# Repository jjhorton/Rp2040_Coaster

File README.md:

# Rp2040_Coaster

## Introduction
The idea was to build a light up drinks coaster, which would sit under a clear glass drinks bottle and light it up in a colorful display, only when the bottle is on top. 

## Building 

The main circuit is built around a [RP2040](https://www.raspberrypi.com/documentation/microcontrollers/rp2040.html), using the WS2812B "Neopixels" as the LEDs to create the colours, and a USB-C connector for power and programming. The PCB is designed using Kicad, and makes use of a simple 2 layer PCB, the examples here are made using JLCPCB, but any should work. 

The control software is written in C and is based of the PIO example from the Raspberry Pi example repo, the colours are generated based on the inputs of the 4 switches under the PCB. If two of the 4 switches are on, the light display begins, fading between pre-generated color pattern, which repeats. 

The PCB is placed under a 3d Printed case, this protects the PCB and electronics from any liquid or condensation on a cold bottle, the case is designed using openscad and the examples shown were printed on an Ender3 3D printed, and it should be possible to produce with most cheap 3D printers. 

## Testing

The software and PCB's fabrication files are built using Github actions, and the artifacts file contains a build of the latest software for uploading to the RP2040 and Gerbers that can be used to produced the PCB's using  

For the case, using the OpenSCAD files in the repo, they are automatically converted into a STL file using a seperate github workflow, with the files downloadable as an artifact from the last time they were run. 

## License 

Code: BSD-3-Clause

PCB/3D Model: CERN Open Hardware Licence Version 2 - Permissive

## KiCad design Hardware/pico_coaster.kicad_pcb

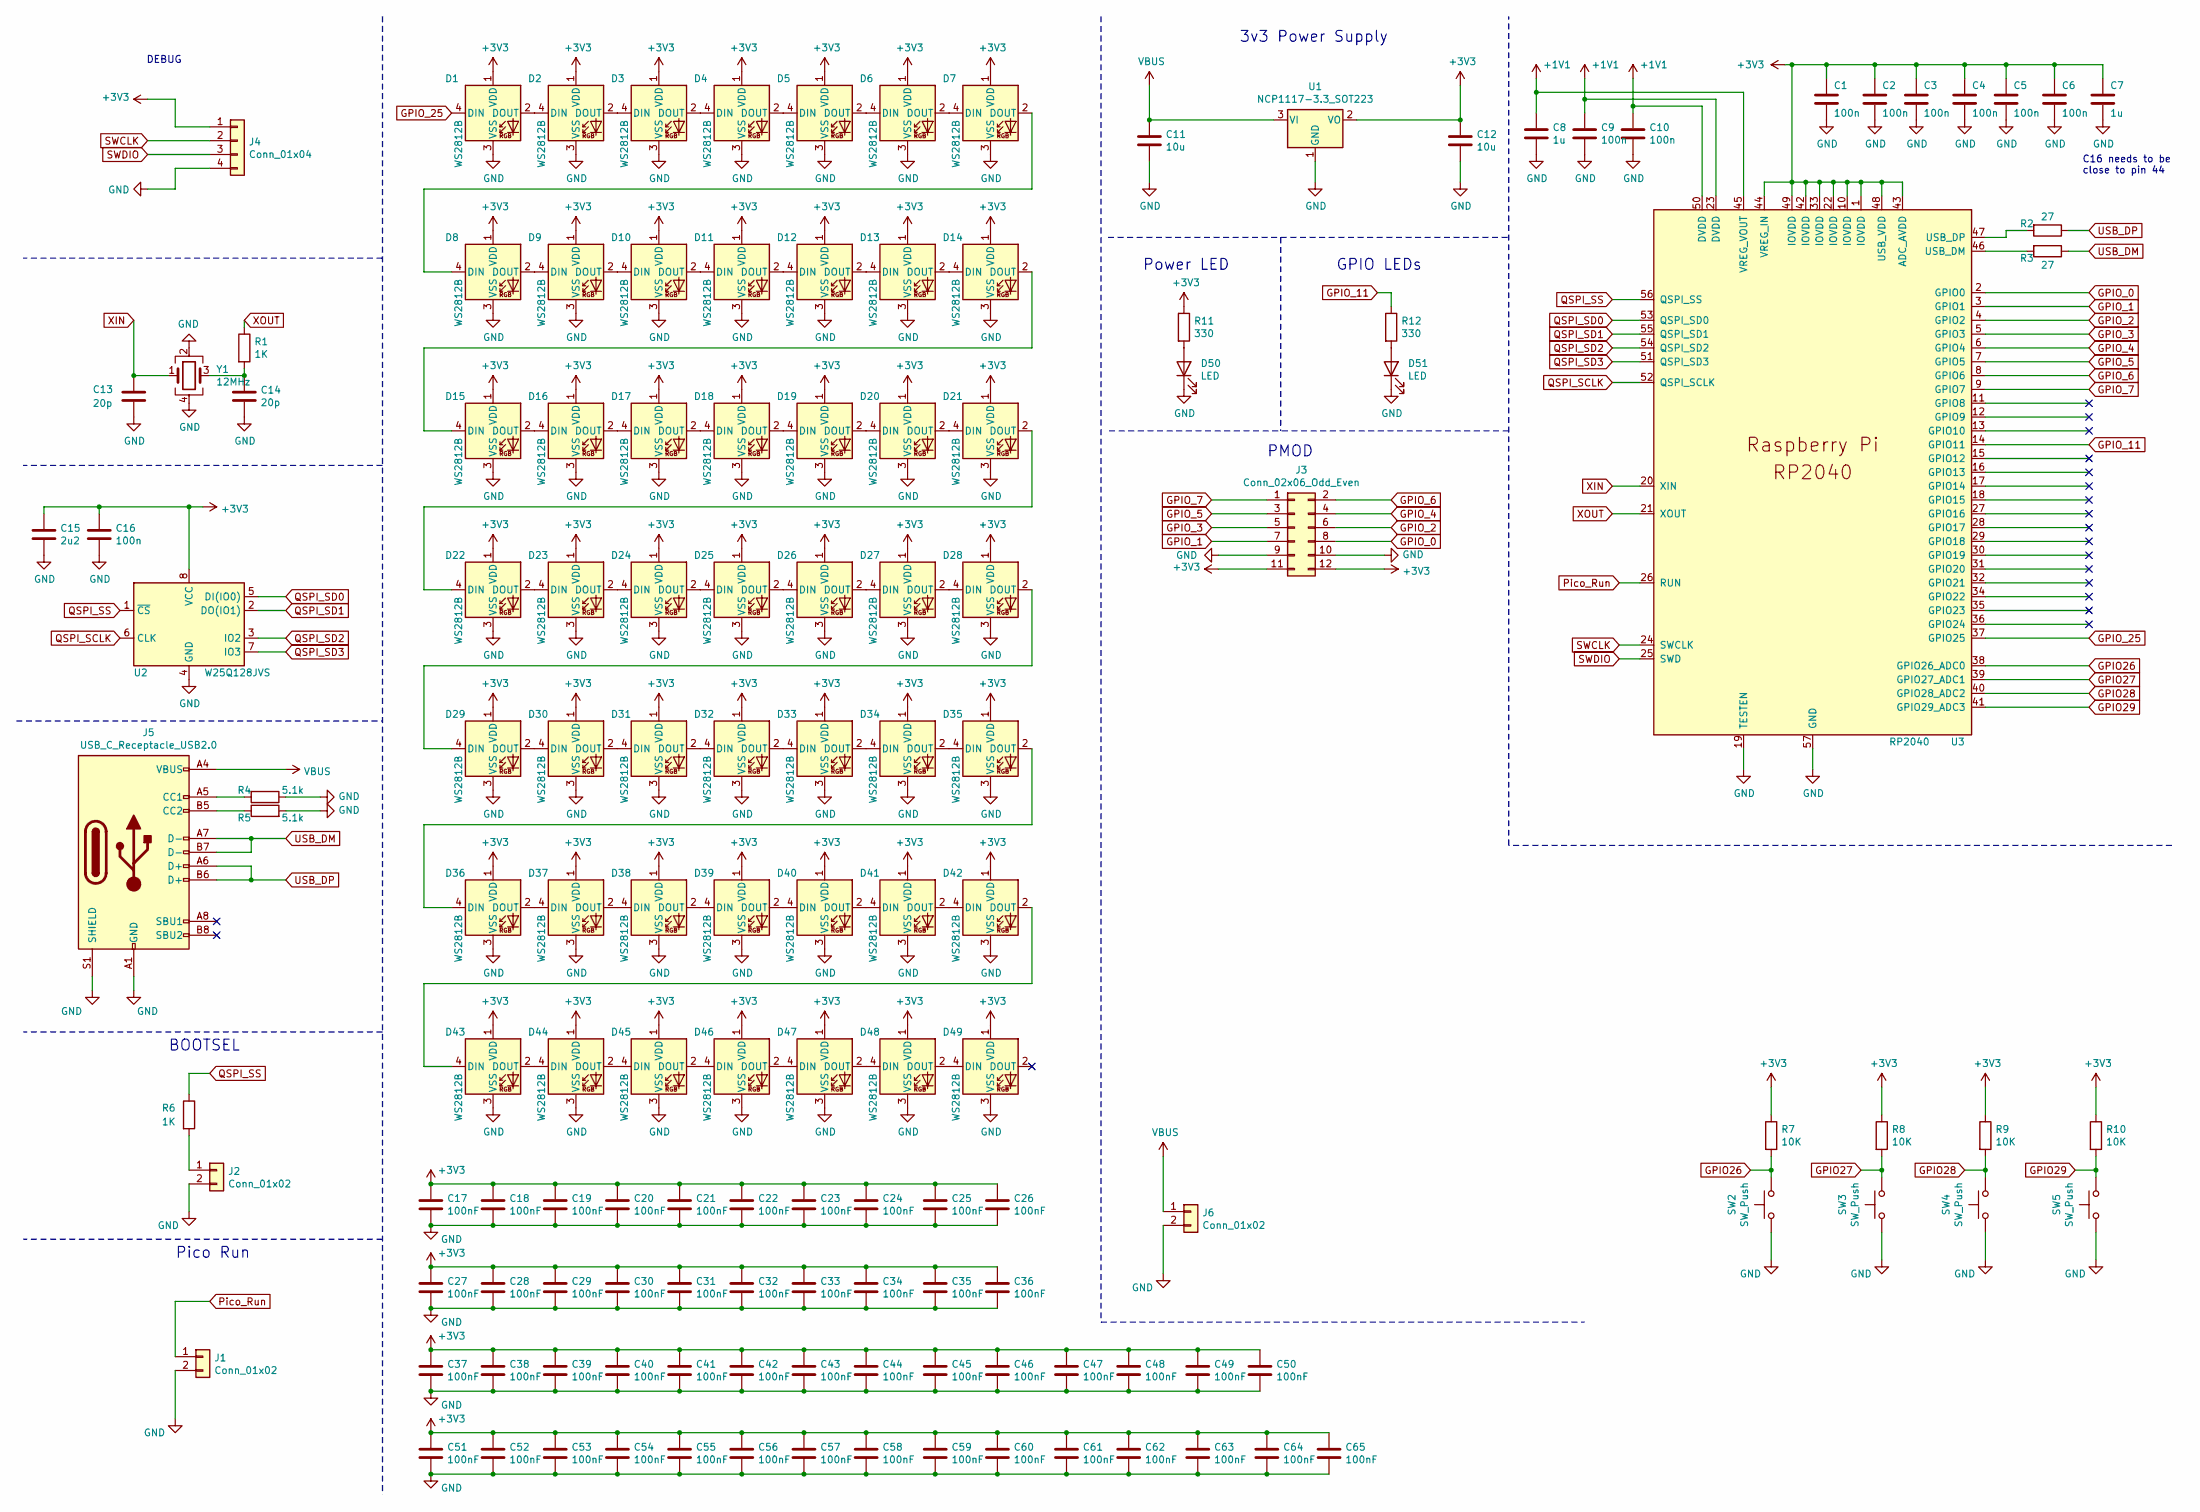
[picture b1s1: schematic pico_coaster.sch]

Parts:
C1, C2, C3, C4, C5, C6, C9, C10, C16: 100n; C_0603_1608Metric
C7, C8: 1u; C_0603_1608Metric
C11, C12: 10u; C_0603_1608Metric
C13, C14: 20p; C_0603_1608Metric
C15: 2u2; C_0603_1608Metric
C17, C18, C19, C20, C21, C22, C23, C24, C25, C26, C27, C28, C29, C30, C31, C32, C33, C34, C35, C36, C37, C38, C39, C40, C41, C42, C43, C44, C45, C46, C47, C48, C49, C50, C51, C52, C53, C54, C55, C56, C57, C58, C59, C60, C61, C62, C63, C64, C65: 100nF; C_0603_1608Metric
D1, D2, D3, D4, D5, D6, D7, D8, D9, D10, D11, D12, D13, D14, D15, D16, D17, D18, D19, D20, D21, D22, D23, D24, D25, D26, D27, D28, D29, D30, D31, D32, D33, D34, D35, D36, D37, D38, D39, D40, D41, D42, D43, D44, D45, D46, D47, D48, D49: WS2812B; LED_WS2812B_PLCC4_5.0x5.0mm_P3.2mm
D50, D51: LED; LED_0603_1608Metric
J1, J2, J6: Conn_01x02; PinHeader_1x02_P2.54mm_Horizontal
J3: Conn_02x06_Odd_Even; PinHeader_2x06_P2.54mm_Vertical
J4: Conn_01x04; PinHeader_1x04_P2.54mm_Vertical
J5: USB_C_Receptacle_USB2.0; USB_C_Receptacle_Amphenol_12401610E4-2A_CircularHoles
R1, R6: 1K; R_0603_1608Metric
R2, R3: 27; R_0603_1608Metric
R4, R5: 5.1k; R_0603_1608Metric
R7, R8, R9, R10: 10K; R_0603_1608Metric
R11, R12: 330; R_0603_1608Metric
SW2, SW3, SW4, SW5: SW_Push; SW_PUSH_6mm_H4.3mm
U1: NCP1117-3.3_SOT223; SOT-223-3_TabPin2
U2: W25Q128JVS; SOIC-8_5.23x5.23mm_P1.27mm
U3: RP2040; RP2040-QFN-56
Y1: 12MHz; Crystal_SMD_SeikoEpson_FA238-4Pin_3.2x2.5mm

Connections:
+1V1: C8.1, C9.1, C10.1, U3.23 (DVDD), U3.45 (VREG_VOUT), U3.50 (DVDD)
+3V3: C1.1, C2.1, C3.1, C4.1, C5.1, C6.1, C7.1, C12.1, C15.1, C16.1, C17.1, C18.1, C19.1, C20.1, C21.1, C22.1, C23.1, C24.1, C25.1, C26.1, C27.1, C28.1, C29.1, C30.1, C31.1, C32.1, C33.1, C34.1, C35.1, C36.1, C37.1, C38.1, C39.1, C40.1, C41.1, C42.1, C43.1, C44.1, C45.1, C46.1, C47.1, C48.1, C49.1, C50.1, C51.1, C52.1, C53.1, C54.1, C55.1, C56.1, C57.1, C58.1, C59.1, C60.1, C61.1, C62.1, C63.1, C64.1, C65.1, D1.1 (VDD), D2.1 (VDD), D3.1 (VDD), D4.1 (VDD), D5.1 (VDD), D6.1 (VDD), D7.1 (VDD), D8.1 (VDD), D9.1 (VDD), D10.1 (VDD), D11.1 (VDD), D12.1 (VDD), D13.1 (VDD), D14.1 (VDD), D15.1 (VDD), D16.1 (VDD), D17.1 (VDD), D18.1 (VDD), D19.1 (VDD), D20.1 (VDD), D21.1 (VDD), D22.1 (VDD), D23.1 (VDD), D24.1 (VDD), D25.1 (VDD), D26.1 (VDD), D27.1 (VDD), D28.1 (VDD), D29.1 (VDD), D30.1 (VDD), D31.1 (VDD), D32.1 (VDD), D33.1 (VDD), D34.1 (VDD), D35.1 (VDD), D36.1 (VDD), D37.1 (VDD), D38.1 (VDD), D39.1 (VDD), D40.1 (VDD), D41.1 (VDD), D42.1 (VDD), D43.1 (VDD), D44.1 (VDD), D45.1 (VDD), D46.1 (VDD), D47.1 (VDD), D48.1 (VDD), D49.1 (VDD), J3.11, J3.12, J4.1, R7.1, R8.1, R9.1, R10.1, R11.1, U1.2 (VO), U2.8 (VCC), U3.1 (IOVDD), U3.10 (IOVDD), U3.22 (IOVDD), U3.33 (IOVDD), U3.42 (IOVDD), U3.43 (ADC_AVDD), U3.44 (VREG_IN), U3.48 (USB_VDD), U3.49 (IOVDD)
GND: C1.2, C2.2, C3.2, C4.2, C5.2, C6.2, C7.2, C8.2, C9.2, C10.2, C11.2, C12.2, C13.2, C14.2, C15.2, C16.2, C17.2, C18.2, C19.2, C20.2, C21.2, C22.2, C23.2, C24.2, C25.2, C26.2, C27.2, C28.2, C29.2, C30.2, C31.2, C32.2, C33.2, C34.2, C35.2, C36.2, C37.2, C38.2, C39.2, C40.2, C41.2, C42.2, C43.2, C44.2, C45.2, C46.2, C47.2, C48.2, C49.2, C50.2, C51.2, C52.2, C53.2, C54.2, C55.2, C56.2, C57.2, C58.2, C59.2, C60.2, C61.2, C62.2, C63.2, C64.2, C65.2, D1.3 (VSS), D2.3 (VSS), D3.3 (VSS), D4.3 (VSS), D5.3 (VSS), D6.3 (VSS), D7.3 (VSS), D8.3 (VSS), D9.3 (VSS), D10.3 (VSS), D11.3 (VSS), D12.3 (VSS), D13.3 (VSS), D14.3 (VSS), D15.3 (VSS), D16.3 (VSS), D17.3 (VSS), D18.3 (VSS), D19.3 (VSS), D20.3 (VSS), D21.3 (VSS), D22.3 (VSS), D23.3 (VSS), D24.3 (VSS), D25.3 (VSS), D26.3 (VSS), D27.3 (VSS), D28.3 (VSS), D29.3 (VSS), D30.3 (VSS), D31.3 (VSS), D32.3 (VSS), D33.3 (VSS), D34.3 (VSS), D35.3 (VSS), D36.3 (VSS), D37.3 (VSS), D38.3 (VSS), D39.3 (VSS), D40.3 (VSS), D41.3 (VSS), D42.3 (VSS), D43.3 (VSS), D44.3 (VSS), D45.3 (VSS), D46.3 (VSS), D47.3 (VSS), D48.3 (VSS), D49.3 (VSS), D50.1 (K), D51.1 (K), J1.2, J2.2, J3.9, J3.10, J4.4, J5.A1 (GND), J5.A12 (GND), J5.B1 (GND), J5.B12 (GND), J5.S1 (SHIELD), J6.2, R4.1, R5.2, SW2.1, SW3.1, SW4.1, SW5.1, U1.1 (GND), U2.4 (GND), U3.19 (TESTEN), U3.57 (GND), Y1.2, Y1.4
GPIO26: R7.2, SW2.2, U3.38 (GPIO26_ADC0)
GPIO27: R8.2, SW3.2, U3.39 (GPIO27_ADC1)
GPIO28: R9.2, SW4.2, U3.40 (GPIO28_ADC2)
GPIO29: R10.2, SW5.2, U3.41 (GPIO29_ADC3)
GPIO_0: J3.8, U3.2 (GPIO0)
GPIO_1: J3.7, U3.3 (GPIO1)
GPIO_2: J3.6, U3.4 (GPIO2)
GPIO_3: J3.5, U3.5 (GPIO3)
GPIO_4: J3.4, U3.6 (GPIO4)
GPIO_5: J3.3, U3.7 (GPIO5)
GPIO_6: J3.2, U3.8 (GPIO6)
GPIO_7: J3.1, U3.9 (GPIO7)
GPIO_11: R12.1, U3.14 (GPIO11)
GPIO_25: D1.4 (DIN), U3.37 (GPIO25)
unnamed: C14.1, R1.2, Y1.3
unnamed: D1.2 (DOUT), D2.4 (DIN)
unnamed: D2.2 (DOUT), D3.4 (DIN)
unnamed: D3.2 (DOUT), D4.4 (DIN)
unnamed: D4.2 (DOUT), D5.4 (DIN)
unnamed: D5.2 (DOUT), D6.4 (DIN)
unnamed: D6.2 (DOUT), D7.4 (DIN)
unnamed: D7.2 (DOUT), D8.4 (DIN)
unnamed: D8.2 (DOUT), D9.4 (DIN)
unnamed: D10.2 (DOUT), D11.4 (DIN)
unnamed: D9.2 (DOUT), D10.4 (DIN)
unnamed: D11.2 (DOUT), D12.4 (DIN)
unnamed: D12.2 (DOUT), D13.4 (DIN)
unnamed: D13.2 (DOUT), D14.4 (DIN)
unnamed: D14.2 (DOUT), D15.4 (DIN)
unnamed: D15.2 (DOUT), D16.4 (DIN)
unnamed: D16.2 (DOUT), D17.4 (DIN)
unnamed: D17.2 (DOUT), D18.4 (DIN)
unnamed: D18.2 (DOUT), D19.4 (DIN)
unnamed: D19.2 (DOUT), D20.4 (DIN)
unnamed: D20.2 (DOUT), D21.4 (DIN)
unnamed: D21.2 (DOUT), D22.4 (DIN)
unnamed: D22.2 (DOUT), D23.4 (DIN)
unnamed: D23.2 (DOUT), D24.4 (DIN)
unnamed: D24.2 (DOUT), D25.4 (DIN)
unnamed: D25.2 (DOUT), D26.4 (DIN)
unnamed: D26.2 (DOUT), D27.4 (DIN)
unnamed: D27.2 (DOUT), D28.4 (DIN)
unnamed: D28.2 (DOUT), D29.4 (DIN)
unnamed: D29.2 (DOUT), D30.4 (DIN)
unnamed: D30.2 (DOUT), D31.4 (DIN)
unnamed: D31.2 (DOUT), D32.4 (DIN)
unnamed: D32.2 (DOUT), D33.4 (DIN)
unnamed: D33.2 (DOUT), D34.4 (DIN)
unnamed: D34.2 (DOUT), D35.4 (DIN)
unnamed: D35.2 (DOUT), D36.4 (DIN)
unnamed: D36.2 (DOUT), D37.4 (DIN)
unnamed: D37.2 (DOUT), D38.4 (DIN)
unnamed: D38.2 (DOUT), D39.4 (DIN)
unnamed: D39.2 (DOUT), D40.4 (DIN)
unnamed: D40.2 (DOUT), D41.4 (DIN)
unnamed: D41.2 (DOUT), D42.4 (DIN)
unnamed: D42.2 (DOUT), D43.4 (DIN)
unnamed: D43.2 (DOUT), D44.4 (DIN)
unnamed: D44.2 (DOUT), D45.4 (DIN)
unnamed: D45.2 (DOUT), D46.4 (DIN)
unnamed: D46.2 (DOUT), D47.4 (DIN)
unnamed: D47.2 (DOUT), D48.4 (DIN)
unnamed: D48.2 (DOUT), D49.4 (DIN)
unnamed: D50.2 (A), R11.2
unnamed: D51.2 (A), R12.2
unnamed: J2.1, R6.2
unnamed: J5.A5 (CC1), R4.2
unnamed: J5.B5 (CC2), R5.1
unnamed: R2.2, U3.47 (USB_DP)
unnamed: R3.2, U3.46 (USB_DM)
Pico_Run: J1.1, U3.26 (RUN)
QSPI_SCLK: U2.6 (CLK), U3.52 (QSPI_SCLK)
QSPI_SD0: U2.5 (DI(IO0)), U3.53 (QSPI_SD0)
QSPI_SD1: U2.2 (DO(IO1)), U3.55 (QSPI_SD1)
QSPI_SD2: U2.3 (IO2), U3.54 (QSPI_SD2)
QSPI_SD3: U2.7 (IO3), U3.51 (QSPI_SD3)
QSPI_SS: R6.1, U2.1 (~CS), U3.56 (QSPI_SS)
SWCLK: J4.2, U3.24 (SWCLK)
SWDIO: J4.3, U3.25 (SWD)
USB_DM: J5.A7 (D-), J5.B7 (D-), R3.1
USB_DP: J5.A6 (D+), J5.B6 (D+), R2.1
VBUS: C11.1, J5.A4 (VBUS), J5.A9 (VBUS), J5.B4 (VBUS), J5.B9 (VBUS), J6.1, U1.3 (VI)
XIN: C13.1, U3.20 (XIN), Y1.1
XOUT: R1.1, U3.21 (XOUT)

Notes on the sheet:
PMOD
Pico Run
BOOTSEL
DEBUG
C16 needs to be close to pin 44
3v3 Power Supply
GPIO LEDs
Power LED

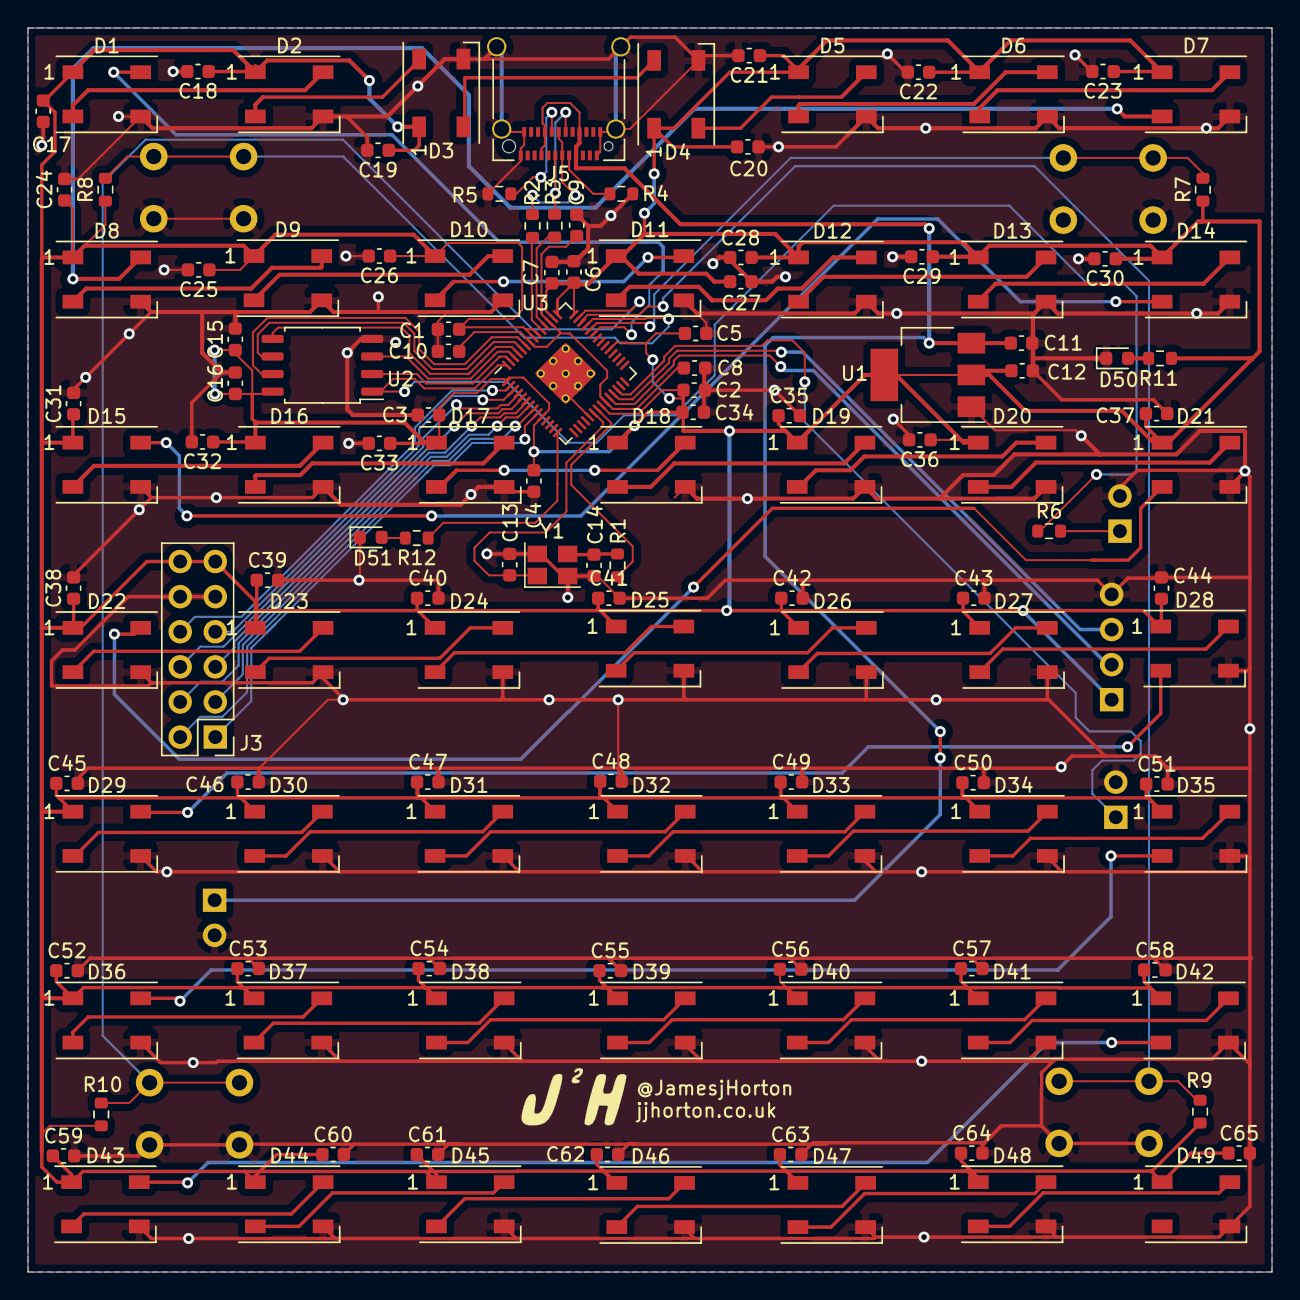
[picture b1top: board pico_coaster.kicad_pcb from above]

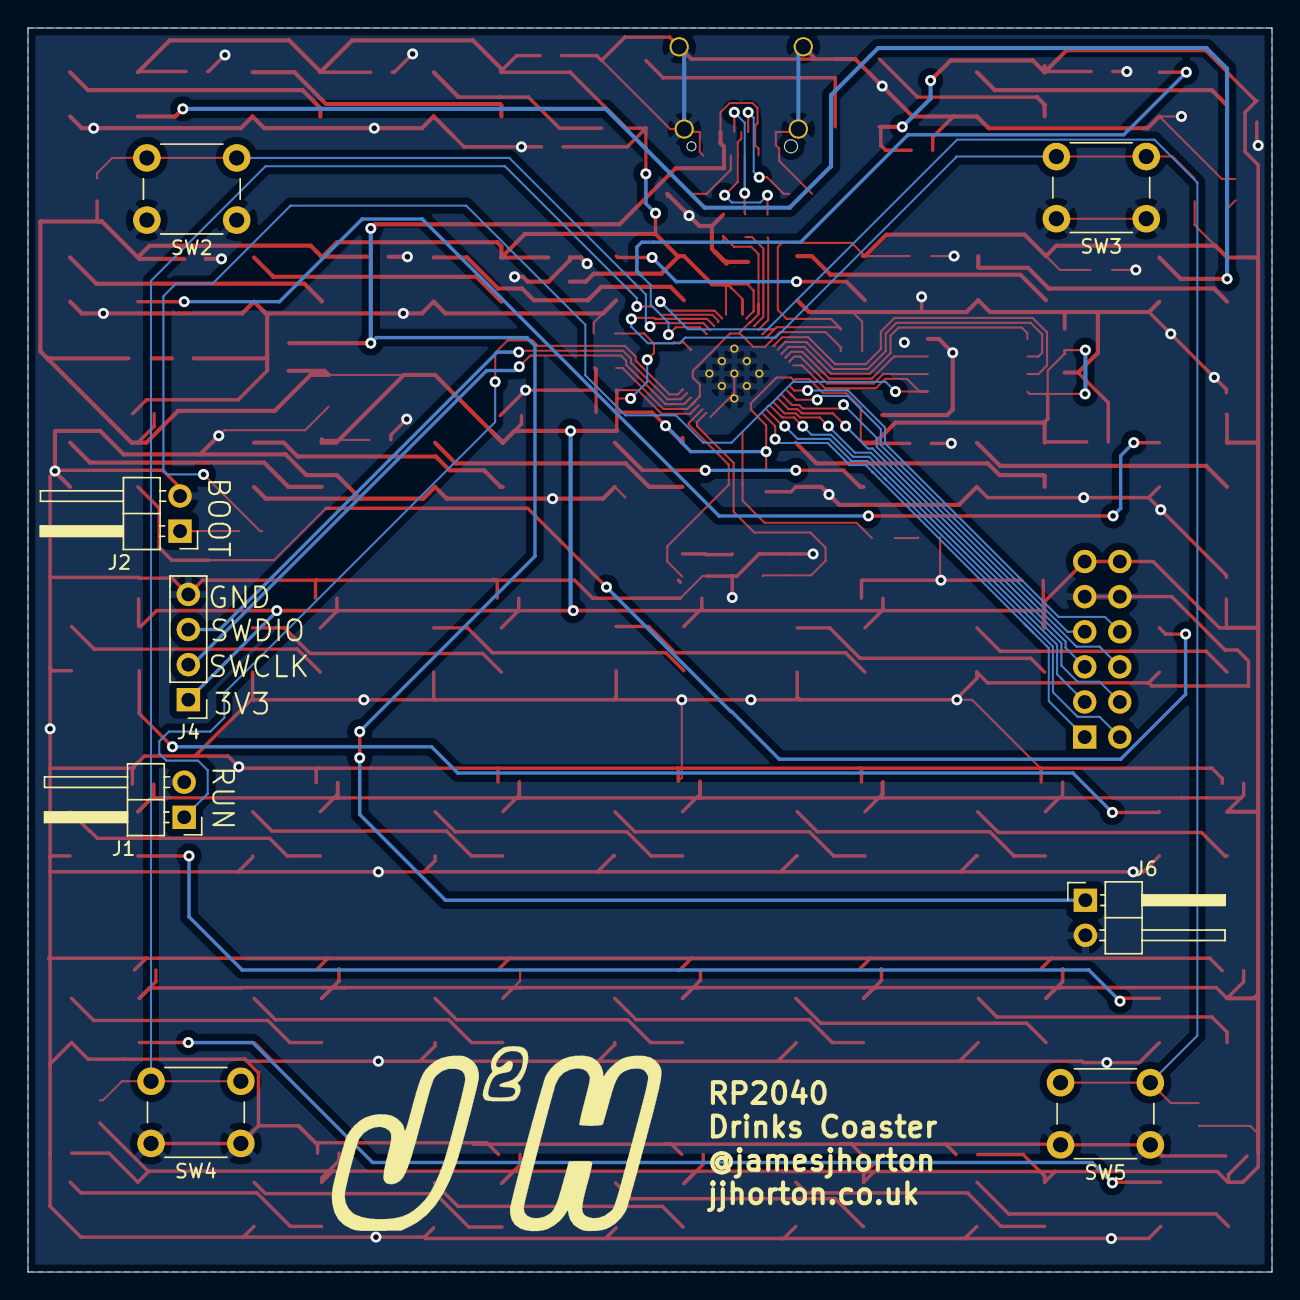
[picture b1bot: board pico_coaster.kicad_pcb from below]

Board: 2 copper layers, 90.0 x 90.0 mm, 142 parts (8 on the bottom side), 87 nets.

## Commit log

2021-10-10 Pervious schematic and layout
2021-10-10 reduce Pmod connectors from 3 to 1
2021-10-10 Add the workflow file for the PCB and software
2021-10-10 Add Kibot configuration file
2021-10-10 Rename the workflow
2021-11-12 prior layout changes
2021-11-12 add USB-c connector on top layer
2021-11-12 route the Resistors for the USB Connector
2021-11-12 Routing RP2040 Caps, Memory and PMod Connector
2021-11-12 Route the GPIO buttons
2021-11-12 Routing Bottom row of RGB LEDs
2021-11-12 Routing Bottom row 3 RGB LEDs completed
2021-11-12 Finish layout for the top three LED rows
2021-11-12 Swap Boot/Run buttons for pin headers
2021-11-12 fix missing 3v3 connection
2021-11-12 add front gnd fill zone and logo on front
2021-11-12 Fix DRC errors
2021-11-12 fix unconnected DRC errors
2021-11-12 Add LED flash as basic software for CI to pass
2021-11-12 Fix Software CI workflow error
2021-11-12 Add gpio init and set direction
2021-11-12 fix type in gpio_init()
2021-11-12 fix error with brackets
2021-11-12 Add git ignore file
2021-11-12 Speeling correction
2021-11-12 Make workflow run only on pull requests
2021-11-14 Add 2.54mm power in connector
2021-11-14 update chematic with number
2021-11-26 redraw rear ground plane
2021-11-26 relocate gnd via near signal path
2021-11-27 Add in basic Software example using neopixels
2021-11-28 Update the software to have random colours on button press
2021-12-01 Add the OpenSCAD initial top case design
2021-12-01 Add workflow for automatically building stl of the case
2021-12-01 Correct the file name typo
2021-12-01 and set functions and use button control
2021-12-06 update the case to allow space for LEDs and USB connector
2021-12-08 Case design edits, not completed
2021-12-16 change clk capasitors
2021-12-16 update cap values in pcb file
2021-12-17 Increase USb recess and higher sides
2021-12-17 update to include colour map and all red when off
2021-12-18 adjust USB port size and hight of sides
2022-02-27 add building description to the repo
2022-02-27 add images to the repo readme file
2022-02-27 Add copyright details at the top of the code
2022-02-27 Add license to the readme file
2022-02-27 Add space between license
